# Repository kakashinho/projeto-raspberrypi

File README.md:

<h1 align="center">🅿️ Estacionamento Inteligente</h1>

<p align="center">
Raspberry Pi, sensores e um painel web para controlar entradas, saídas e vagas.
</p>

<p align="center">
<br>
<sub>Primeiro protótipo</sub>
</p>

<p align="center">
<a href="docs/projeto_fisico/video/demonstracao-projeto-fisico.mp4"><b>▶️ Vídeo</b></a> &nbsp;·&nbsp;
<a href="codigo/sistema/"><b>💻 Código</b></a> &nbsp;·&nbsp;
<a href="guia/guia_equipe.pdf"><b>📘 Guia (PDF)</b></a> &nbsp;·&nbsp;
<a href="maquete/"><b>🧱 Maquete</b></a>
</p>

---

## 🎯 Sobre o projeto

Projeto da atividade **Apresentação do projeto Raspberry**. O caso escolhido é um **estacionamento de supermercado**, em que o que importa é a **saída**: quem sai precisa estar liberado (no protótipo, pelo painel ou pelo potenciômetro da guarita).

| 🚗 Entrada | 🚧 Saída | 🖥️ Painel |
| :-- | :-- | :-- |
| O sensor percebe o carro. Se há vaga, a cancela abre e fecha depois que o carro passa. | O porteiro libera a saída pelo painel ou pela guarita. | Vagas livres, movimento da semana e temperatura do pátio. |

---

## 🧭 Como funciona

```mermaid
flowchart LR
  subgraph S["📡 Sensores"]
    direction TB
    DHT["🌡️ DHT11<br/>temperatura e umidade"]
    US["📏 HC-SR04<br/>presença"]
    POT["🎛️ Potenciômetro e botão<br/>guarita"]
  end

  subgraph R["🍓 Raspberry Pi"]
    direction TB
    MAIN["🧠 main.py<br/>decide e aciona"]
    CANC["🚧 Cancelas, LED e buzzer"]
    NODE["⚙️ Node.js + Express<br/>server.js"]
    DB[("🗄️ SQLite<br/>estacionamento.db")]
    PAINEL["🖥️ Painel web<br/>public/index.html"]
  end

  NAV["💻 Navegador<br/>PC ou celular"]

  DHT --> MAIN
  US --> MAIN
  POT --> MAIN
  MAIN --> CANC
  MAIN -- "API HTTP /api" --> NODE
  NODE <--> DB
  NODE --> PAINEL
  NAV -- "raspberrypi.local:3000" --> PAINEL

  classDef sensor fill:#FFF4D6,stroke:#E0A800,color:#3D2E00
  classDef pi fill:#E3F2FD,stroke:#1E6FD9,color:#0B2E59
  classDef server fill:#E8F5E9,stroke:#2E7D32,color:#123B16
  classDef painel fill:#F3E5F5,stroke:#8E24AA,color:#3A1347
  classDef user fill:#ECEFF1,stroke:#546E7A,color:#263238
  class DHT,US,POT sensor
  class MAIN,CANC pi
  class NODE,DB server
  class PAINEL painel
  class NAV user
  style S fill:#FFFBEA,stroke:#E0A800
  style R fill:#F4F9FF,stroke:#1E6FD9
```

**Em ordem, o que acontece:**

1. 🚗 Um carro chega à entrada e o sensor percebe.
2. 🧠 A Raspberry decide: se há vaga, abre a cancela. Se está lotado, acende o LED vermelho.
3. ⚙️ A Raspberry registra a entrada ou saída no servidor.
4. 🖥️ O painel atualiza as vagas, e a pessoa vê tudo no navegador.

> 🎨 **Cores:** 🟡 sensores · 🔵 Raspberry Pi · 🟢 servidor e banco · 🟣 painel · ⚪ navegador

---

## 👥 Trabalho em equipe

| Integrante | Tarefa | Redes |
| :-- | :-- | :-- |
| *Ana Graciano* | 1️⃣ Cancelas |   |
| *Laís Zanardi* | 2️⃣ Presença |   |
| *Pedro Nascimento* | 3️⃣ Guarita manual |   |
| *Lucas Inácio* | 4️⃣ Sinalização |   |
| *João Moura* | 5️⃣ Ambiente |   |
| *Gustavo Rosa* | 6️⃣ Lógica |   |
| *João Silva* | 7️⃣ Backend |   |
| *Enzo Gabriel de Paula* | 8️⃣ Frontend |   |

---

## 🔧 Como ficou na prática

<p align="center">
<br>
<sub>Fluxo de desenvolvimento, na ordem em que foi feito</sub>
</p>

<p align="center">
<br>
<sub>Placa de interface em 3D, feita no KiCad, com a etiqueta PIMACO</sub>
</p>

<details>
<summary><b>▶️ Ver a placa de outros ângulos</b></summary>

<table align="center">
<tr>
<td align="center"><br><sub>Vista de cima</sub></td>
<td align="center"><br><sub>Vista inclinada</sub></td>
</tr>
<tr>
<td align="center"><br><sub>Lado esquerdo</sub></td>
<td align="center"><br><sub>Lado direito</sub></td>
</tr>
</table>

</details>

<details>
<summary><b>▶️ Antes da montagem: a bancada de testes</b></summary>

<table>
<tr>
<td align="center"><br><sub>Pi, placa, servos e sensor</sub></td>
<td align="center"><br><sub>Vista de cima</sub></td>
</tr>
<tr>
<td align="center"><br><sub>Vista lateral</sub></td>
<td align="center"><br><sub>Materiais: EVA preto e branco</sub></td>
</tr>
</table>

</details>

<details>
<summary><b>▶️ Depois da montagem: o protótipo completo</b></summary>

<table>
<tr>
<td align="center"><br><sub>Detalhe da maquete</sub></td>
<td align="center"><br><sub>Painel web</sub></td>
</tr>
</table>

</details>

---

## 🧱 Projeto de montagem da maquete

O projeto que mostra como montar a maquete. Usa só papelão, EVA e papel impresso, e as peças são planas, para caberem numa pasta.

<p align="center">
<br>
<sub>Para girar o modelo, abra <a href="maquete/maquete_3d.html">maquete_3d.html</a></sub>
</p>

<details>
<summary><b>🔍 Mais ângulos da maquete</b></summary>

<table align="center">
<tr>
<td align="center"><br><sub>Lado da entrada</sub></td>
<td align="center"><br><sub>Por trás, em diagonal</sub></td>
</tr>
<tr>
<td align="center"><br><sub>Frente da guarita</sub></td>
<td align="center"><br><sub>Painel de perto (MANUAL e STATUS)</sub></td>
</tr>
</table>

</details>

- 📖 [Passo a passo para montar](maquete/LEIA-ME.md)
- 🧭 [Proposta e decisões](maquete/FASE1_proposta.md)
- 🖨️ [Arquivos para imprimir](maquete/impressao/)

---

## 🚀 Como rodar o sistema

Os comandos ficam na pasta [`codigo/sistema/`](codigo/sistema/), e rodam na Raspberry Pi com a placa de interface:

```bash
npm install            # só na primeira vez
./web.sh start         # painel em http://raspberrypi.local:3000
python3 -u main.py     # parte física (cancelas, LED e buzzer)
```

<details>
<summary><b>🧪 Testar uma peça por vez</b></summary>

```bash
python3 teste_isolado.py led     # também: buzzer, servo_entrada, servo_saida, botao, pot, distancia, dht
```

Pare o `main.py` antes de testar uma peça.

</details>

---

## 📚 Onde ler mais

| Documento | Para que serve |
| :-- | :-- |
| 📘 [Guia da equipe](guia/index.html) | Passo a passo de cada tarefa, com figuras |
| 📕 [Guia em PDF](guia/guia_equipe.pdf) | A mesma versão, para imprimir |
| 📦 [Transferência](docs/transferencia.md) | O que tem no repositório e como usar cada parte |
| 🧾 [Lista de materiais](docs/lista_de_materiais.csv) | Componentes da placa |
| 🔌 [Placa de interface](hardware/README.md) | Projeto da placa no KiCad, arquivos e etiquetas |
| 🧪 [Códigos de partida](codigo/starter/README.md) | Um esqueleto por tarefa, para começar |
| ⚙️ [Código final](codigo/sistema/README.md) | O sistema que roda na Raspberry Pi |

---

<details>
<summary><b>🔎 Saiba mais</b></summary>

<p align="center">
<br>
<sub>Pinos GPIO usados pela placa, na numeração BCM</sub>
</p>

<p align="center">
<br>
<sub>Regras de funcionamento do sistema</sub>
</p>

<p align="center">
<br>
<sub>Quem faz cada ação no painel e na Raspberry</sub>
</p>
<p align="center">As rotas exatas estão em <a href="codigo/sistema/server.js"><code>codigo/sistema/server.js</code></a>.</p>

<p align="center">
<br>
<sub>Testes feitos antes da entrega</sub>
</p>

<p align="center">
<br>
<sub>Pastas do repositório: o que cada uma guarda</sub>
</p>

</details>

---

<p align="center"><a href="#topo">⬆️ Voltar ao topo</a></p>

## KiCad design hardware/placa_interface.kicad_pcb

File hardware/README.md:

# 🔌 Hardware: placa de interface

Projeto da placa que encaixa no Raspberry Pi e reúne os sensores e atuadores do estacionamento. Feita no **KiCad 10**.

## 📂 O que tem aqui

| Arquivo | Para que serve |
| :-- | :-- |
| `placa_interface.kicad_pro` e `.kicad_pcb` | Projeto da placa no KiCad (abra o `.kicad_pro`) |
| `montagem_placa_interface.pdf` | Lado dos componentes, lado do cobre, etiqueta e lista de montagem |
| `trilhas_tamanho_real_A4.pdf` | Trilhas em tamanho real (1:1), para conferir sobre a placa |
| `etiquetas_A_B_pimaco6282.pdf` | Etiquetas para a folha Pimaco 6282 |
| `etiquetas_A_B_folha_cheia.pdf` | Mesmas etiquetas, em folha cheia |
| `etiquetas_teste_papel_comum.pdf` | Teste de impressão em papel comum, antes de gastar a folha |
| `previas/` | Imagens de pré-visualização (montagem, trilhas, etiquetas) |
| `gerador/` | Scripts que geram os arquivos acima |

## 🧭 Pinos principais

As posições dos pinos estão em `gerador/design.py`, que é a **fonte da verdade** da placa. Os pinos usados no software estão em [`codigo/sistema/pinos.py`](../codigo/sistema/pinos.py).

## 🔁 Gerar de novo

Com o KiCad 10 instalado (e o PyMuPDF para os PDFs), rode na pasta `hardware/gerador`:

```bash
"C:\Program Files\KiCad\10.0\bin\python.exe" gerar_placa.py ../
python exportar.py ../
```

A imagem 3D da placa pode ser renderizada com o próprio KiCad, por exemplo:

```bash
kicad-cli pcb render -o previas/placa_3d.png --side top --rotate "-45,0,30" --background transparent placa_interface.kicad_pcb
```

## 🧾 Lista de materiais

A lista completa de componentes está em [`docs/lista_de_materiais.csv`](../docs/lista_de_materiais.csv).

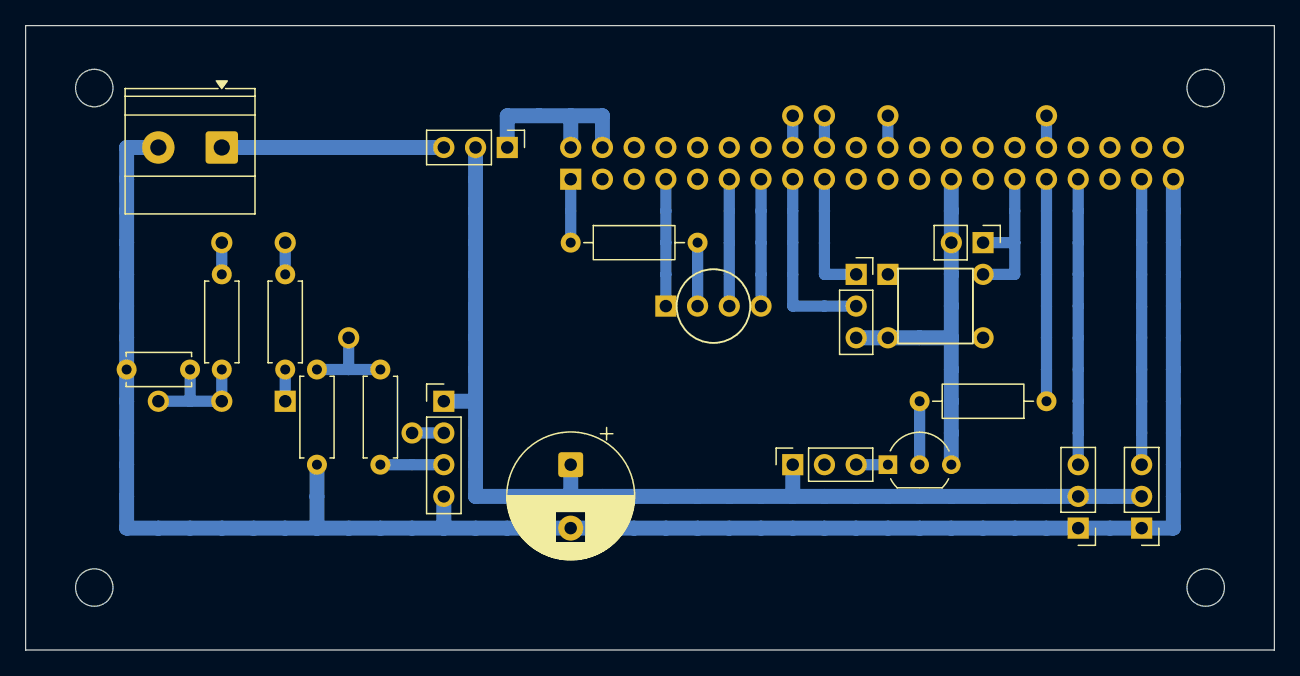
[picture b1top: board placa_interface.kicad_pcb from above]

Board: 2 copper layers, 100.0 x 50.0 mm, 25 parts (1 on the bottom side), 23 nets.

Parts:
C1: 100nF; C_Disc_D5.0mm_W2.5mm_P5.00mm
C2: 470uF 25V; CP_Radial_D10.0mm_P5.00mm
D1: LED RGB anodo comum
J1: Barra fêmea 2x20 pinos longos (stacking); PinSocket_2x20_P2.54mm_Vertical
J2: Servo 1; PinHeader_1x03_P2.54mm_Vertical
J3: Servo 2; PinHeader_1x03_P2.54mm_Vertical
J4: HC-SR04; PinHeader_1x04_P2.54mm_Vertical
J5: DHT11; PinSocket_1x03_P2.54mm_Vertical
J6: Buzzer; PinSocket_1x03_P2.54mm_Vertical
J7: Borne 5V externa; TerminalBlock_Phoenix_MKDS-1,5-2-5.08_1x02_P5.08mm_Horizont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
J8: Botão externo; PinHeader_1x02_P2.54mm_Vertical
JP1: Seletor 5V (jumper); PinHeader_1x03_P2.54mm_Vertical
Q1: BC337; TO-92_Inline_Wide
R1, R2: 10k; R_Axial_DIN0207_L6.3mm_D2.5mm_P7.62mm_Horizontal
R3, R4: 330; R_Axial_DIN0207_L6.3mm_D2.5mm_P7.62mm_Horizontal
R5: 330; R_Axial_DIN0207_L6.3mm_D2.5mm_P10.16mm_Horizontal
R6: 1k; R_Axial_DIN0207_L6.3mm_D2.5mm_P10.16mm_Horizontal
RV1: Pot 10k linear
SW1: Chave táctil
W1, W2, W3, W4: fio encapado (lado cobre)

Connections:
+3V3: J1.1, J1.17, J5.1, R5.1
+5V: C2.1, J2.2, J3.2, J4.1, J6.1, JP1.2
+5V_EXT: J7.1, JP1.3
+5V_RPI: J1.2, J1.4, JP1.1
BUZ_NEG: J6.3, Q1.1
ECHO_5V: J4.3, R3.2
GND: C1.2, C2.2, J1.6, J1.9, J1.14, J1.20, J1.25, J1.30, J1.34, J1.39, J2.1, J3.1, J4.4, J5.3, J7.2, J8.2, Q1.3, R4.2, SW1.3
GPIO4_LED_R: D1.1, J1.7
GPIO5_BOTAO: J1.29, J8.1, SW1.2
GPIO6_BUZZER: J1.31, R6.1
GPIO12_POT_LEIT: J1.32, R2.2, W4.1
GPIO13_SERVO1: J1.33, J2.3
GPIO17_LED_G: D1.3, J1.11
GPIO22_DHT: J1.15, J5.2
GPIO23_TRIG: J1.16, J4.2, W1.1
GPIO24_ECHO: J1.18, R3.1, R4.1, W2.1
GPIO25_POT_CARGA: J1.22, R1.2, W3.1
GPIO26_SERVO2: J1.37, J3.3
GPIO27_LED_B: D1.4, J1.13
LED_A: D1.2, R5.2
POT_1: R1.1, RV1.1
POT_X: C1.1, R2.1, RV1.2, RV1.3
Q1_BASE: Q1.2, R6.2

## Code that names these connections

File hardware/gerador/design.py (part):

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PI_PIN_NET = {
    1: "+3V3", 17: "+3V3", 2: "+5V_RPI", 4: "+5V_RPI",
    6: "GND", 9: "GND", 14: "GND", 20: "GND", 25: "GND", 30: "GND", 34: "GND", 39: "GND",
    7: "GPIO4_LED_R", 11: "GPIO17_LED_G", 13: "GPIO27_LED_B", 15: "GPIO22_DHT",
    16: "GPIO23_TRIG", 18: "GPIO24_ECHO", 22: "GPIO25_POT_CARGA", 32: "GPIO12_POT_LEIT",
    29: "GPIO5_BOTAO", 31: "GPIO6_BUZZER", 33: "GPIO13_SERVO1", 37: "GPIO26_SERVO2",
}
PI_JUMPER_GROUPS = [["6", "9", "14", "20", "25", "30", "34", "39"], ["1", "17"], ["2", "4"]]

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         pads={"1": ("J6", "POT_1"), "2": ("J4", "POT_X"), "3": ("J2", "POT_X")}),
    dict(ref="C1", value="100nF", lib=("Capacitor_THT", "C_Disc_D5.0mm_W2.5mm_P5.00mm"), pitch2=5.08,
         pads={"1": ("I3", "POT_X"), "2": ("I1", "GND")}),
    dict(ref="R2", value="10k", lib=P7, pads={"1": ("I4", "POT_X"), "2": ("F4", "GPIO12_POT_LEIT")}),
    dict(ref="R1", value="10k", lib=P7, pads={"1": ("I6", "POT_1"), "2": ("F6", "GPIO25_POT_CARGA")}),
    dict(ref="J4", value="HC-SR04", lib=HDR4,
         pads={"1": ("J11", "+5V"), "2": ("K11", "GPIO23_TRIG"), "3": ("L11", "ECHO_5V"), "4": ("M11", "GND")}),
    dict(ref="R3", value="330", lib=P7, pads={"1": ("I9", "GPIO24_ECHO"), "2": ("L9", "ECHO_5V")}),
    dict(ref="R4", value="330", lib=P7, pads={"1": ("I7", "GPIO24_ECHO"), "2": ("L7", "GND")}),
    dict(ref="R5", value="330", lib=P10, pads={"1": ("E15", "+3V3"), "2": ("E19", "LED_A")}),
    dict(ref="D1", value="LED RGB anodo comum", lib=None, kind="led",
         pads={"1": ("G18", "GPIO4_LED_R"), "2": ("G19", "LED_A"),
               "3": ("G20", "GPIO17_LED_G"), "4": ("G21", "GPIO27_LED_B")}),
    dict(ref="J5", value="DHT11", lib=SKT3,
         pads={"1": ("F24", "+3V3"), "2": ("G24", "GPIO22_DHT"), "3": ("H24", "GND")}),
    dict(ref="SW1", value="Chave táctil", lib=None, kind="sw",
         pads={"1": ("F25", None), "2": ("F28", "GPIO5_BOTAO"), "3": ("H25", "GND"), "4": ("H28", None)}),
    dict(ref="J8", value="Botão externo", lib=HDR2, pads={"1": ("E28", "GPIO5_BOTAO"), "2": ("E27", "GND")}),
    dict(ref="R6", value="1k", lib=P10, pads={"1": ("J30", "GPIO6_BUZZER"), "2": ("J26", "Q1_BASE")}),
    dict(ref="Q1", value="BC337", lib=("Package_TO_SOT_THT", "TO-92_Inline_Wide"),
         pads={"1": ("L25", "BUZ_NEG"), "2": ("L26", "Q1_BASE"), "3": ("L27", "GND")}),
    dict(ref="J6", value="Buzzer", lib=SKT3,
         pads={"1": ("L22", "+5V"), "2": ("L23", None), "3": ("L24", "BUZ_NEG")}),
    dict(ref="J2", value="Servo 1", lib=HDR3,
         pads={"1": ("N31", "GND"), "2": ("M31", "+5V"), "3": ("L31", "GPIO13_SERVO1")}),
    dict(ref="J3", value="Servo 2", lib=HDR3,
         pads={"1": ("N33", "GND"), "2": ("M33", "+5V"), "3": ("L33", "GPIO26_SERVO2")}),
]

JUMPERS = [
    ("W1", "GPIO23_TRIG", "A22", "K10", 106.3),
    ("W2", "GPIO24_ECHO", "A23", "H8", 105.6),
    ("W3", "GPIO25_POT_CARGA", "A25", "E6", 104.9),
    ("W4", "GPIO12_POT_LEIT", "A30", "E4", 104.2),
]

def run(a, b):
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            path("C27", "L27"), path("H27", "H24")],
    "+3V3": [path("C15", "E15"), path("C23", "F23", "F24")],
    "LED_A": [path("E19", "G19")],
    "GPIO4_LED_R": [path("C18", "G18")],
    "GPIO17_LED_G": [path("C20", "G20")],
    "GPIO27_LED_B": [path("C21", "G21")],
    "GPIO22_DHT": [path("C22", "G22", "G24")],
    "GPIO23_TRIG": [path("B22", "A22"), path("K10", "K11")],
    "GPIO24_ECHO": [path("B23", "A23"), path("H8", "I8"), path("I7", "I9")],
    "GPIO25_POT_CARGA": [path("B25", "A25"), path("E6", "F6")],
    "GPIO12_POT_LEIT": [path("B30", "A30"), path("E4", "F4")],
    "POT_X": [path("J2", "J4"), path("I3", "J3"), path("I4", "J4")],
    "POT_1": [path("I6", "J6")],
    "ECHO_5V": [path("L9", "L11")],
    "GPIO5_BOTAO": [path("C29", "F29", "F28"), path("E29", "E28")],
    "GPIO6_BUZZER": [path("C30", "J30")],
    "Q1_BASE": [path("J26", "L26")],
    "BUZ_NEG": [path("L25", "L24")],
    "GPIO13_SERVO1": [path("C31", "L31")],
    "GPIO26_SERVO2": [path("C33", "L33")],
}

POWER_NETS = {"+5V", "+5V_RPI", "+5V_EXT", "GND"}
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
